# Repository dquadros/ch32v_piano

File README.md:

# Piano com CH32V002 

(english documentation at the end)

## Português

A ideia básica deste projeto é usar o PWM de um microcontrolador para tocar uma nota conforme a tecla apertada. A inspiração veio de um kit chinês que utiliza um 555.

### Hardware

Eu utilizei um CH32V002A4M6, um microprocessador RISC-V de 32 bits, operando a 48MHz, com 4 kbytes de RAM e 16 kbytes de Flash e encapsulamento SOP16. É uma escolha certamente exagerada para o projeto, mas foi baseada no meu interesse pelo CH32V00x e ter 50 destes chips na gaveta. O CH32V003A4M6, com menos memória, provavelmente seria mais apropriado.

Após algumas experiências, optei por pegar a saída do PWM (uma onda quadrada), passar por um filtro RC e amplificar usando um transistor S8050.

Os botões estão todos ligados a uma única entrada analógica. A tecla apertada é inferida a partir da tensão presente na entrada.

Um trimpot é usado para realizar a afinação e um LED foi acrescentado para o debug.

A alimentação pode ser feita pelo conector de programação ou (no caso da PCI) por um conector micro USB.

### Software

O software foi desenvolvido com o ch32vfun, uma infraestrutura de baixo nível (a programação é feita em C, acessando diretamente os registradores do microcontrolador).

No momento em que escrevo isso, a maioria dos exemplos no ch32Vfun é para o CH32V003 e requer ajustes para os demais modelos (como o CH32V002).

A programação do ADC para a leitura dos botões e do trimpot é relativamente simples. O código realiza várias leituras consecutivas para tentar pegar valores estáveis.

A programação do PWM é mais trabalhosa, mas é simples mudar a frequência uma vez feita a iniciação.

No uso normal, o trimpot de afinação é lido somente na iniciação e usado para ajustar todas as notas. Ligando o circuito com uma tela pressionada, entra-se no modo de afinação. Uma nota é tocada continuamente e sua frequência é atualizada periodicamente conforme a posição do trimpot.

### Placa de Circuito Impresso

Uma placa foi projetada com o Kicad e está atualmente em produção.

### Diretórios

Este repositório possui os seguintes diretórios:

* Hardware: esquema e projeto da PCI, feito com o Kicad 10
* Imagens: logotipo usado na PCI e imagem renderizada da PCI
* Outros: planilha excel para cálculo da programação do PWM
* Software: fontes e executáveis

## English

The basic idea behind this project is to use a microcontroller's PWM to play a note corresponding to the key being pressed. The inspiration came from a Chinese kit that uses a 555 timer.

### Hardware

I used a CH32V002A4M6, a 32-bit RISC-V microcontroller operating at 48 MHz with 4 KB of RAM and 16 KB of Flash in an SOP16 package. It is certainly an overkill for the project, but the choice was driven by my interest in the CH32V00x series and the fact that I had 50 of these chips in my drawer. The CH32V003A4M6, which has less memory, would likely have been more appropriate.

After some experimentation, I opted to take the PWM output (a square wave), pass it through an RC filter, and amplify it using an S8050 transistor.

The buttons are all connected to a single analog input. The specific button pressed is determined based on the voltage present at the input.

A trimpot is used for fine-tuning, and an LED has been added for debugging purposes.

Power can be supplied via the programming connector or (in the case of the PCB) via a micro-USB connector.

### Software

The software was developed using ch32vfun, a low-level framework (programming is done in C, directly accessing the microcontroller's registers).

At the time of writing, most ch32vfun examples are designed for the CH32V003 and require adjustments for other models (such as the CH32V002).

Programming the ADC to read the buttons and the trimpot is relatively straightforward. The code performs several consecutive readings to obtain stable values.

Programming the PWM is more involved, though changing the frequency is simple once initialization is complete.

During normal operation, the tuning trimpot is read only at startup and is used to adjust all notes. Powering on the circuit while a key is pressed enters tuning mode; a note plays continuously, and its frequency is periodically updated based on the trimpot's position.

### Printed Circuit Board

I used Kicad to design a PCB, it is currently in production. 

### Directories

This repository contains the following directories:

* Hardware: schematic and PCB design, created with KiCad 10
* Images: logo used on the PCB and a rendered image of the PCB
* Other: Excel spreadsheet for calculating PWM settings
* Software: source code and executables

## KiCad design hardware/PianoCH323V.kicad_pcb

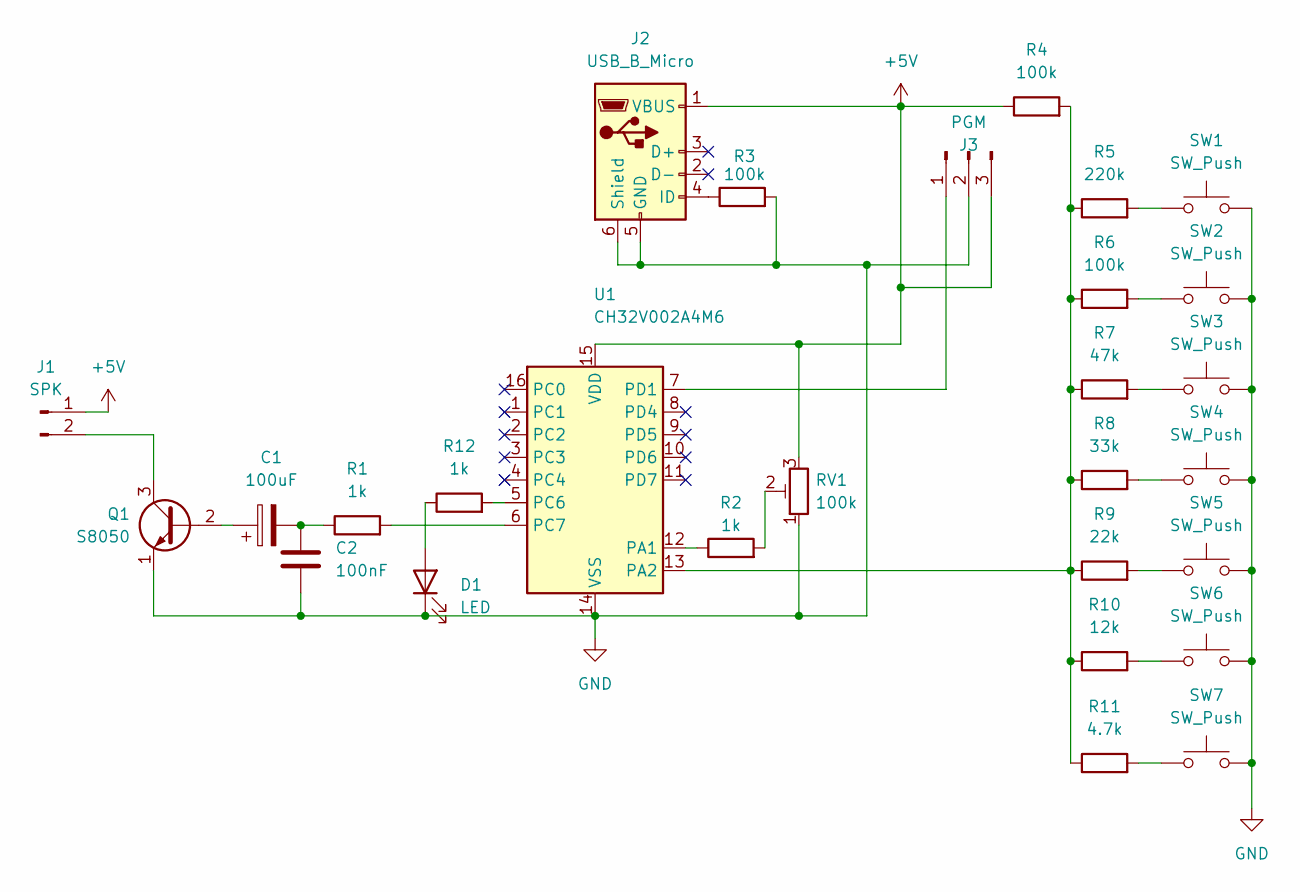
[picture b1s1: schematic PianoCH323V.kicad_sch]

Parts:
C1: 100uF; CP_Radial_D5.0mm_P2.50mm
C2: 100nF; C_Disc_D4.3mm_W1.9mm_P5.00mm
D1: LED; LED_D3.0mm
J1: SPK; PinHeader_1x02_P2.54mm_Horizontal
J2: USB_B_Micro; USB_Micro-B_Wuerth_629105150521_CircularHoles
J3: PGM; PinHeader_1x03_P2.54mm_Horizontal
Q1: S8050; TO-92_Inline
R1, R2, R12: 1k; R_Axial_DIN0207_L6.3mm_D2.5mm_P10.16mm_Horizontal
R3, R4, R6: 100k; R_Axial_DIN0207_L6.3mm_D2.5mm_P10.16mm_Horizontal
R5: 220k; R_Axial_DIN0207_L6.3mm_D2.5mm_P10.16mm_Horizontal
R7: 47k; R_Axial_DIN0207_L6.3mm_D2.5mm_P10.16mm_Horizontal
R8: 33k; R_Axial_DIN0207_L6.3mm_D2.5mm_P10.16mm_Horizontal
R9: 22k; R_Axial_DIN0207_L6.3mm_D2.5mm_P10.16mm_Horizontal
R10: 12k; R_Axial_DIN0207_L6.3mm_D2.5mm_P10.16mm_Horizontal
R11: 4.7k; R_Axial_DIN0207_L6.3mm_D2.5mm_P10.16mm_Horizontal
RV1: 100k; Potentiometer_Runtron_RM-063_Horizontal
SW1, SW2, SW3, SW4, SW5, SW6, SW7: SW_Push; SW_PUSH-12mm
U1: CH32V002A4M6; SOP-16_4.55x10.3mm_P1.27mm

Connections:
+5V: J1.1, J2.1 (VBUS), J3.3, R4.1, RV1.3, U1.15 (VDD)
GND: C2.2, D1.1 (K), J2.5 (GND), J2.6 (Shield), J3.2, Q1.1 (E), R3.2, RV1.1, SW1.2, SW2.2, SW3.2, SW4.2, SW5.2, SW6.2, SW7.2, U1.14 (VSS)
unnamed: C1.2, C2.1, R1.1
unnamed: D1.2 (A), R12.1
unnamed: J1.2, Q1.3 (C)
unnamed: J2.4 (ID), R3.1
unnamed: J3.1, U1.7 (PD1)
unnamed: C1.1, Q1.2 (B)
unnamed: R2.2, RV1.2
unnamed: R5.2, SW1.1
unnamed: R6.2, SW2.1
unnamed: R7.2, SW3.1
unnamed: R8.2, SW4.1
unnamed: R9.2, SW5.1
unnamed: R10.2, SW6.1
unnamed: R11.2, SW7.1
unnamed: R2.1, U1.12 (PA1)
unnamed: R4.2, R5.1, R6.1, R7.1, R8.1, R9.1, R10.1, R11.1, U1.13 (PA2)
unnamed: R12.2, U1.5 (PC6)
unnamed: R1.2, U1.6 (PC7)

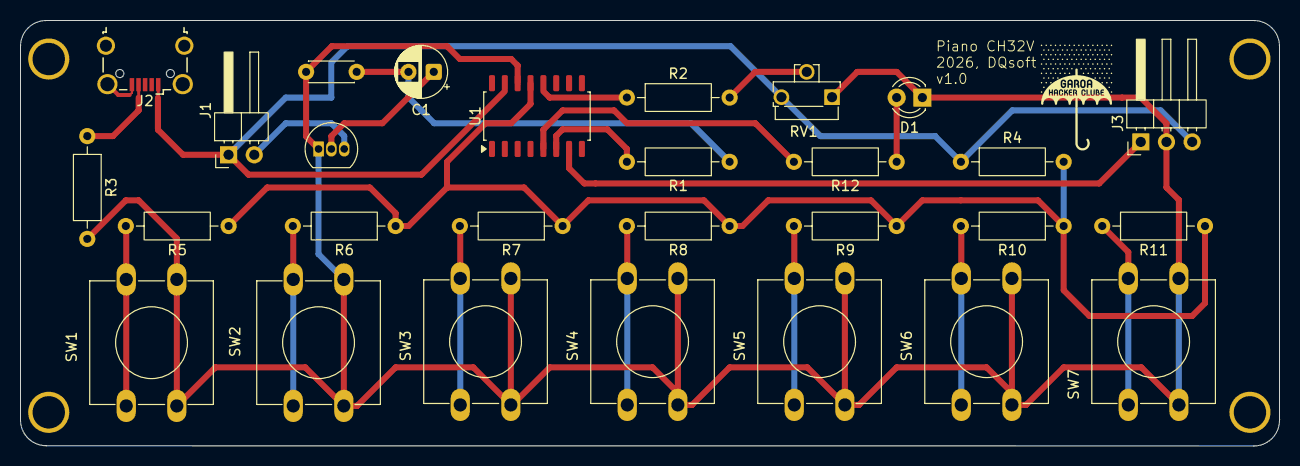
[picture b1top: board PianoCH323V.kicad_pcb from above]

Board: 2 copper layers, 124.5 x 42.1 mm, 28 parts (0 on the bottom side), 20 nets.
